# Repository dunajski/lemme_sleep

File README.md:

# This repository was created to maintain work with projecting and building electronic device.

This simple device  should be able to do few simple tasks listed below:

* generate random numbers which is done with unstable LSB of ADC result :game_die:, 

* measure hold and release button time pressed by user :watch:,

* control vibrating motor with desired timer intervals,

* motor control on diffrent power sources with use of transistor and PWM, 

* smoothly working finite state machine with energy power saving state :battery:.

## Additional informations:

* in this project I used ATmega32 MCU,
* small (10 mm x 2 mm) vibrating motor.

### SUMMARY
* I won't continue develop on this repository.

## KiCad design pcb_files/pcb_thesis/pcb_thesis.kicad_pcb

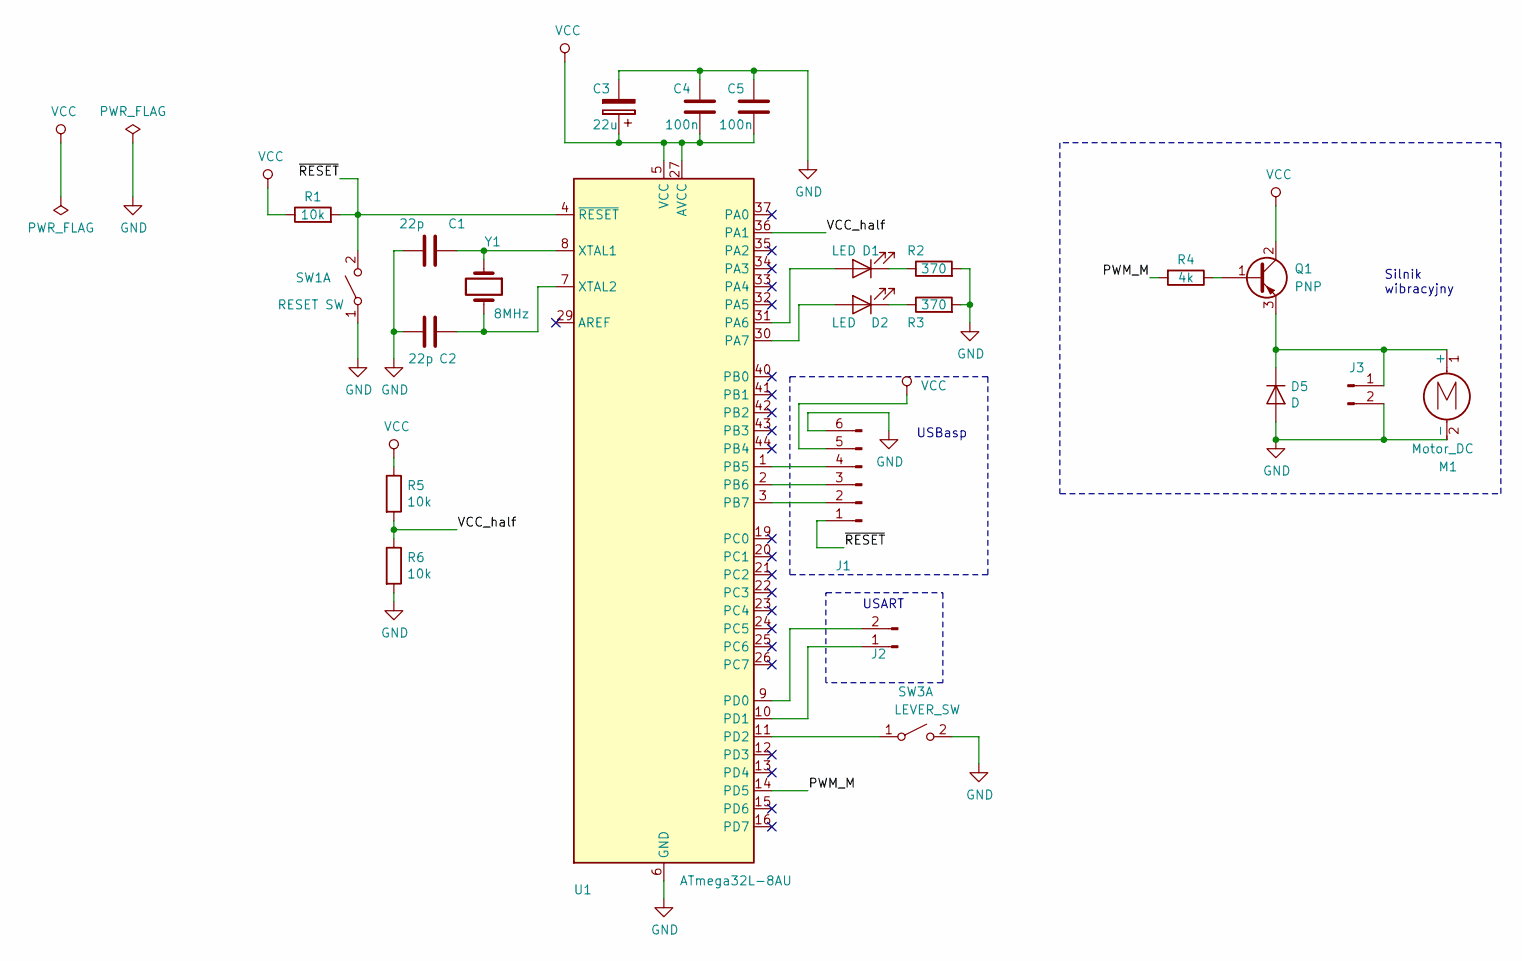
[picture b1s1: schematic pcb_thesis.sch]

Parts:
C1, C2: 22p; R_0805_2012Metric_Pad1.15x1.40mm_HandSolder
C3: 22u; R_1206_3216Metric_Pad1.42x1.75mm_HandSolder
C4, C5: 100n; R_0805_2012Metric_Pad1.15x1.40mm_HandSolder
D1, D2: LED; LED_0805_2012Metric_Pad1.15x1.40mm_HandSolder
D5: D; D_SMC_Handsoldering
J1: goldpin 1x6; PinHeader_1x06_P2.54mm_Horizontal
J2, J3: goldpin 1x2; PinHeader_1x02_P2.54mm_Horizontal
M1: Motor_DC
Q1: PNP; SOT-223
R1, R5, R6: 10k; R_1206_3216Metric_Pad1.42x1.75mm_HandSolder
R2, R3: 370; R_0805_2012Metric_Pad1.15x1.40mm_HandSolder
R4: 4k; R_0805_2012Metric_Pad1.15x1.40mm_HandSolder
SW1: RESET SW; SW_SPST_EVQPE1
SW3: LEVER_SW; MYSWITCHWITHLEWER
U1: ATmega32L-8AU; TQFP-44_10x10mm_P0.8mm
Y1: 8MHz; Crystal_SMD_HC49-SD_HandSoldering

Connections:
/PWM_M: R4.2, U1.14 (PD5)
/VCC_half: R5.2, R6.1, U1.36 (PA1)
/~RESET: J1.1, R1.2, SW1.2 (B), U1.4 (~RESET)
GND: C1.1, C2.1, C3.2, C4.1, C5.1, D5.2 (A), J1.6, J3.2, M1.2 (-), R2.2, R3.2, R6.2, SW1.1 (A), SW3.2 (B), U1.6 (GND), U1.18 (GND), U1.28 (GND), U1.39 (GND)
unnamed: C1.2, U1.8 (XTAL1), Y1.1
unnamed: C2.2, U1.7 (XTAL2), Y1.2
unnamed: D1.1 (K), R2.1
unnamed: D1.2 (A), U1.31 (PA6)
unnamed: D2.1 (K), R3.1
unnamed: D2.2 (A), U1.30 (PA7)
unnamed: D5.1 (K), J3.1, M1.1 (+), Q1.3 (E)
unnamed: J1.2, U1.3 (PB7)
unnamed: J1.3, U1.2 (PB6)
unnamed: J1.4, U1.1 (PB5)
unnamed: J2.1, U1.10 (PD1)
unnamed: J2.2, U1.9 (PD0)
unnamed: Q1.1 (B), R4.1
unnamed: SW3.1 (A), U1.11 (PD2)
VCC: C3.1, C4.2, C5.2, J1.5, Q1.2 (C), R1.1, R5.1, U1.5 (VCC), U1.17 (VCC), U1.27 (AVCC), U1.38 (VCC)

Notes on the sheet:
USART
Silnik wibracyjny
USBasp

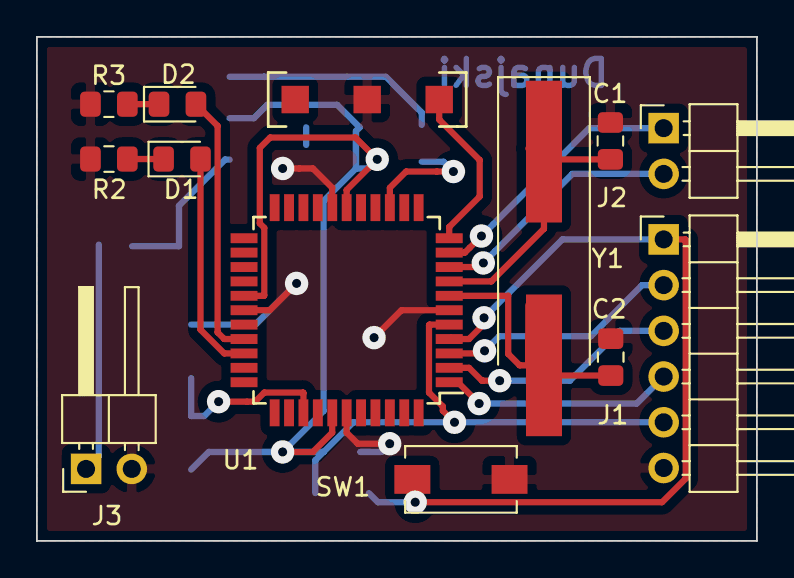
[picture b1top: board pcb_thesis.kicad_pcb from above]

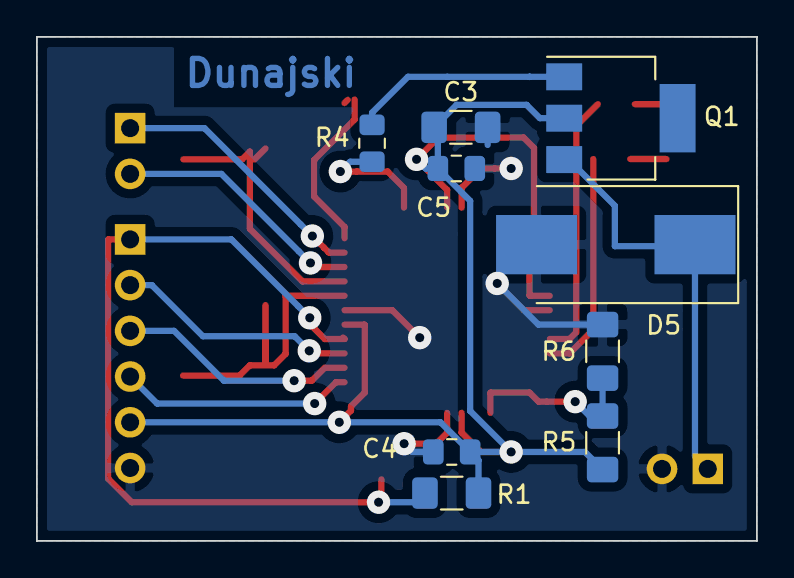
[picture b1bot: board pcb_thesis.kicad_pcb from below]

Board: 2 copper layers, 40.0 x 28.0 mm, 22 parts (9 on the bottom side), 19 nets.

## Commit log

2019-01-16 GitHub synchro test
2019-01-16 Added some line to synchro GitHub test
2019-01-16 Commit and Push via Eclipse test
2019-01-16 next test wanna see it, added uart init function
2019-01-16 Added types.h for future use
2019-01-16 some refactor old code, ouch
2019-01-16 added macros from main to types.h separate communication files
2019-01-17 Added some files, separate functionality, check copy-paste values
2019-01-17 reafctored
2019-01-21 added some pcb scheme files
2019-01-28 added some io configuration etc
2019-01-31 Uart tested on converter 9600/8/N/1
2019-02-02 added key action with debounce
2019-02-08 Update communication.c
    joooo kodzik do domu do usuniecia
2019-04-07 powrot do kodu, problem z 0 0 0 0 ADC
2019-04-09 drukowanie, ADCH i ADCL na terminal po kliknieciu, losowanie co klik
2019-04-14 draw number by click one button, make it automatically
2019-04-15 dodano plik z probkami xls, sprawdzic czy dla wiekszej ilosci probek tez wychodzi taka nierownomiernosc
2019-04-16 ~60k probek wylosowanych, ADC teraz uruchamiane poprzez key wartosci zapisywane sa do tablicy zakomentowano losowanie duzej ilosci probek, juz nie uzywane
2019-04-17 wstepna implementacja fsm urzadzenia, todo obsluga klawisza dla kazdego z poszczegolnych stanow
2019-04-17 added readme with typora editor
2019-04-18 obsluga klawisza w stanie interakcji wip
    dodano "substany" klawisza w trakcie interakcji, uin16_t powinien moc przechowac czas release i holda maks to az 26 sekund, nie przewiduje tak gluch probek nadawania stad jezeli ktos przekroczy ten s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
2019-04-18 update readme.md
    Added description about simple task that device should be able to do
2019-04-23 mierzenie interakcji wip
    proba zmierzenia czasu wcisniecia i odpuszczenia przycisku, na ten moment zbyt zakrecone ify sie wykladaja, ostatnie wcisniecie tj. 5te przerywa cala sekwencje. testy za pomoca debug led, czasy ISR s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
2019-04-24 added sending uint16 values via UART
    Dodano mozliwosc wysylania, przy uzyciu UART wartosci uint16 w celu zasymulowania sobie czasu wcisniecia i odpuszczenia przycisku. TODO: test measure hold and release
2019-04-25 added short typedefs
2019-05-01 added instruction and fixed pointer out of bound
    I added xmind map to show how state ST_INTERAKCJA works. I found out that I wasnt changing back position of pointer that I use so then after about 10 sequences program crashes.
2019-05-01 refactor and comments
2019-05-02 added mindmap with behaviour of device, activity rating WIP
2019-05-07 Added posibility to Put Sint32 values to serial
    Those values are needed to send for future estimating actual activity of device user.
2019-05-08 device fsm improvemenet
    przygotwac FSM prawidlowe na razie zostaw ocene, ze zawsze zwraca ze uzytkownik :OK: powtorzyl sekwencje. funkcja do porownywarki. funkcja do poszerzenia ilosci czasu z wylosowanych wartosci.
2019-05-09 updated schematic files to be more actual
2019-05-15 updated pcb files
    divided schematic into parts and discarded option with source of energy but schematic is prepared for this feature
2019-05-15 description and small changes to schematic
2019-05-16 added some footprints and edgees for little chassis
2019-05-21 added few footprints and created two pcb boards WIP
2019-05-23 pcb in progress
2019-05-23 adding smooth fsm implementation wip
    state sa zaimplementowane oprocz OCENY i IDLE'a ale dodatkowo niech smooothly przechodzi miedzy nimi wtedy zajmiemy sie ocena
2019-05-28 designing pcb WIP
2019-05-29 fsm implementation wip
2019-05-30 przesunieto jedno zlacze blizej srodka plytki
    w rogach black boxa znajduja sie mocowanie dwoch czesci nie moga
    zachodzic na elementy bo nie ma tyle miejsca
2019-06-12 Przygotowanie do debugowania
    Przygotowane do testowania, powinno plynnie przechodzic pomiedzy stanami
    sygnalizujac w jakim stanie jest na terminalu. Brakuje obslugi oceny,
    testow poprwanosco dzialania.
2019-06-20 Poprawa w dzialaniu maszyny stanow
    Work in progress.
2019-06-20 Dodanie komentarzy
    Lekki refactor dodanie komentarzy
2019-06-21 Kod potrzebowal oczyszczenia
    Refactor czyszczenie, work in progress
2019-06-21 W koncu dziala maszyna stanow urzadzenia
    Wciaz nie ma zaimplementowanej oceny interakcji, wiec po prostu pomija
    ten etap i przechodzi znow do uspienia ukladu. Po uspieniu nalezy
    trzykrotnie wcisnac przycisk aby wybudzic. Jesli w ciagu 10 sekund
    urzadzenie nie otrzyma 3 wcisniec ponownie przejdzie w stan oszczedzania
    energii. Brakuje PWMa do sterowania silnika zaleznie od zasilania i
    oceny. Nadaje sie do mastera.
2019-06-22 Dodanie inicjalizacji PWMa
    Timer0/2 zajete, do sterowania PWMa zastosuje Timer1, 16bitowy. Tryb
    Fast PWM, OC1A pin do sterowania silnikiem. Dodano obsluge atomic
    blokiem zapisu do zmiennej 16bitowej volatile (na potrzebe rejestru
    OCR1A).
2019-06-22 Added some information to README section
    Found some bugs in description and added small information to clear.
2019-06-23 Added functionality to change ADC properties
    There is DC motor that need to be controlled with PWM because diffrent
    device's supply voltage. So to do that we need to switch between ADC
    configurations (one for drawing variables and second for measuring
    supply voltage). In datasheet manufacturer wrote that second adc
    conversion result after changing channel or ref voltage is viable. So
    second Conversion value is stored.
2019-06-24 Dodanie funkcji do obliczania i ustawiania OCR1A
    Funkcja na podstawie wyniku z ADC oblicza wartosc jaka musi przyjac PWM
    zeby silnik mial odpowiednie zasilanie. Zasilanie nie moze byc powyzej
    3,4v.
2019-06-30 Wprowadzenie sterowania napieciem zasilania
    Ze wzgledu na rozne napiecie zasilania e.g. 3v3,3v7,5v nalezy
    wprowadzic ograniczenie napiecia na zaciskach silnika. Stad sterowanie
    PWMem zaleznie od napiecia zasilania. Gdy napiecie jest ponizej
    granicznego (3v5) to takie samo napiecie jest na zaciskach silnika
    natomiast dla wyzszych napiec jest ograniczone. Testowane na LED.
2019-06-30 Dodano zabezpieczenie przed przekrocczeniem czasu
    Hold i Release teraz ma maksymalny czas wcisniecia 10 sekund, powyzej
    tego czasu zostaje zapisane 0xFFFF do tablicy z wartosciami
2019-07-01 Dodano funkcje do obslugi wartosci losowych
    Teraz po losowaniu wartosci z wyloosowania sa ladowane do tablicy oraz
    mnozone/poszerzone do interwale 500 ms. Kilka linii do debugowania.
2019-07-01 Szybki refactor
2019-07-02 Wlaczenie oprocz LED silnika wibracyjnego
    Wczesniejsze proby byly bez silnika na ledzie, teraz jest silnik.
2019-08-11 zrzut
2019-08-11 synchro zrodel
2019-08-21 gamma and beta and alfa factors
2019-08-26 some cleaning before more changes
2019-08-26 Zmiana czasow wibracji
    W celu uproszczenia powtarzania narzucono tylko czasy mozliwe 1, 2.5, 4
2019-08-28 Troche poprawek z debouncingiem
2019-09-02 Rozna ilosc wibracji w sekwencji wip
2019-09-03 Dodano blokade maksymalnych czasow
    Maksymalny czas calej odpowiedzi oraz czasu oczekiwania na reakcje
    uzytkownika wynosi 30 sekund
2019-09-05 Dodanie opoznienia pomiedzy wylosowanie a wibrowaniem
2019-09-10 Podawliny pod testy delayow
    Sprawdz czy wykona siedem opoznienie pomiedzy ocena a kolejnym losowaniem.
2019-09-10 Proba ustawiania czasu pomiedzy sekwencjami
    Potrzeba roznego czasu pomiedzy sekwencjami, albo switch albo obliczanie, na ten moment switch z SO do wytestowania. Kod potrzebuje refaktoru i to niesamowicie, rename'y i pogrupowanie w strutury bo 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
2019-09-11 Poprawka w kasowaniu ilosci sekwencji
2019-09-11 Wytestowane przerwy pomiedzy sekwencjami
2019-09-19 Dodano obsluge zmniejszania ilosci wibracji w sekwencji
    Kod wola o refaktor i zaczyna zyc wlasnym zyciem, zgrupowano niektore
    zmienne w strukture.
2019-09-19 Poprawki w opisie
2019-09-26 Testing some auto-tools
2019-10-16 Przygotowanie plikow do wytrawiania plytki
2019-10-30 Added all pcb files
    Mysle ze to wszystkie juz... i nie bedzie zmian.
2019-10-30 Zmiana sekwencji na bardziej stala
    Sekwencja jest uproszczona w celu sprawdzenia wplywu samego sygnalu na jakos zasypiania.
2019-11-01 Proba przeniesienia sie na vscode
    Kompilacja jakos przeszla, czas na wgranie avrdudem i reszta.
2019-11-23 Refactor WiP
2019-12-14 Formatting pc this should be reverted
2020-01-11 Poprawka w orientacji tranzystora
    Zamiana wyprowadzen tranzystora PNP na schemacie. Kardynalny blad z
    zamiana emitera z kolektorem. Uwaga, zmiana jest tylko na schemacie na
    plytce PCB pozostala stara wersja ze wzgledu na to ze plytka zostala
    juz wykonana. Rozwiazaniem tego problemu moze byc jakis trick z
    lutowaniem na plytce albo znalezie tranzystora z zamienonymi
    wyprowadzeniami.
2020-01-11 Kilka zmian testowych do pomiaru napiecia silnika
    Te zmiany nie powinny byc w finalnej wersji FW, a na pewno nie w takiej
    postaci natomiast zostaly uzyte do testowanie polaczen i mierzenia
    napiec na zaciskach silnika przed fizycznym uzyciem go.
2020-01-11 Ignorowanie plikow z kompilacji oraz Makefile
    Ze wzgledu na przejscie z Eclipse, utworzono wlasnoreczny skrypt
    Makefile do kompilacji zrodel oraz wgrywania pliku .hex na MCU.
2020-01-18 Description update
2020-01-22 Poprawka w orientacji tranzystora
    Niestety nieopatrznie nie sprawdzilem w jaki sposob zostal polaczony
    tranzystor. Na szczescie blad jest tylko w kolejnosci wyprowadzen,
    udalo sie to zalutowac natomiast blad wciaz widnieje na PCB.
2020-01-22 Dodanie listy wymaganych zmian
2020-01-22 Dodatkowe informacje na przyszlosc
2020-06-01 Added "bye-bye" info :)
